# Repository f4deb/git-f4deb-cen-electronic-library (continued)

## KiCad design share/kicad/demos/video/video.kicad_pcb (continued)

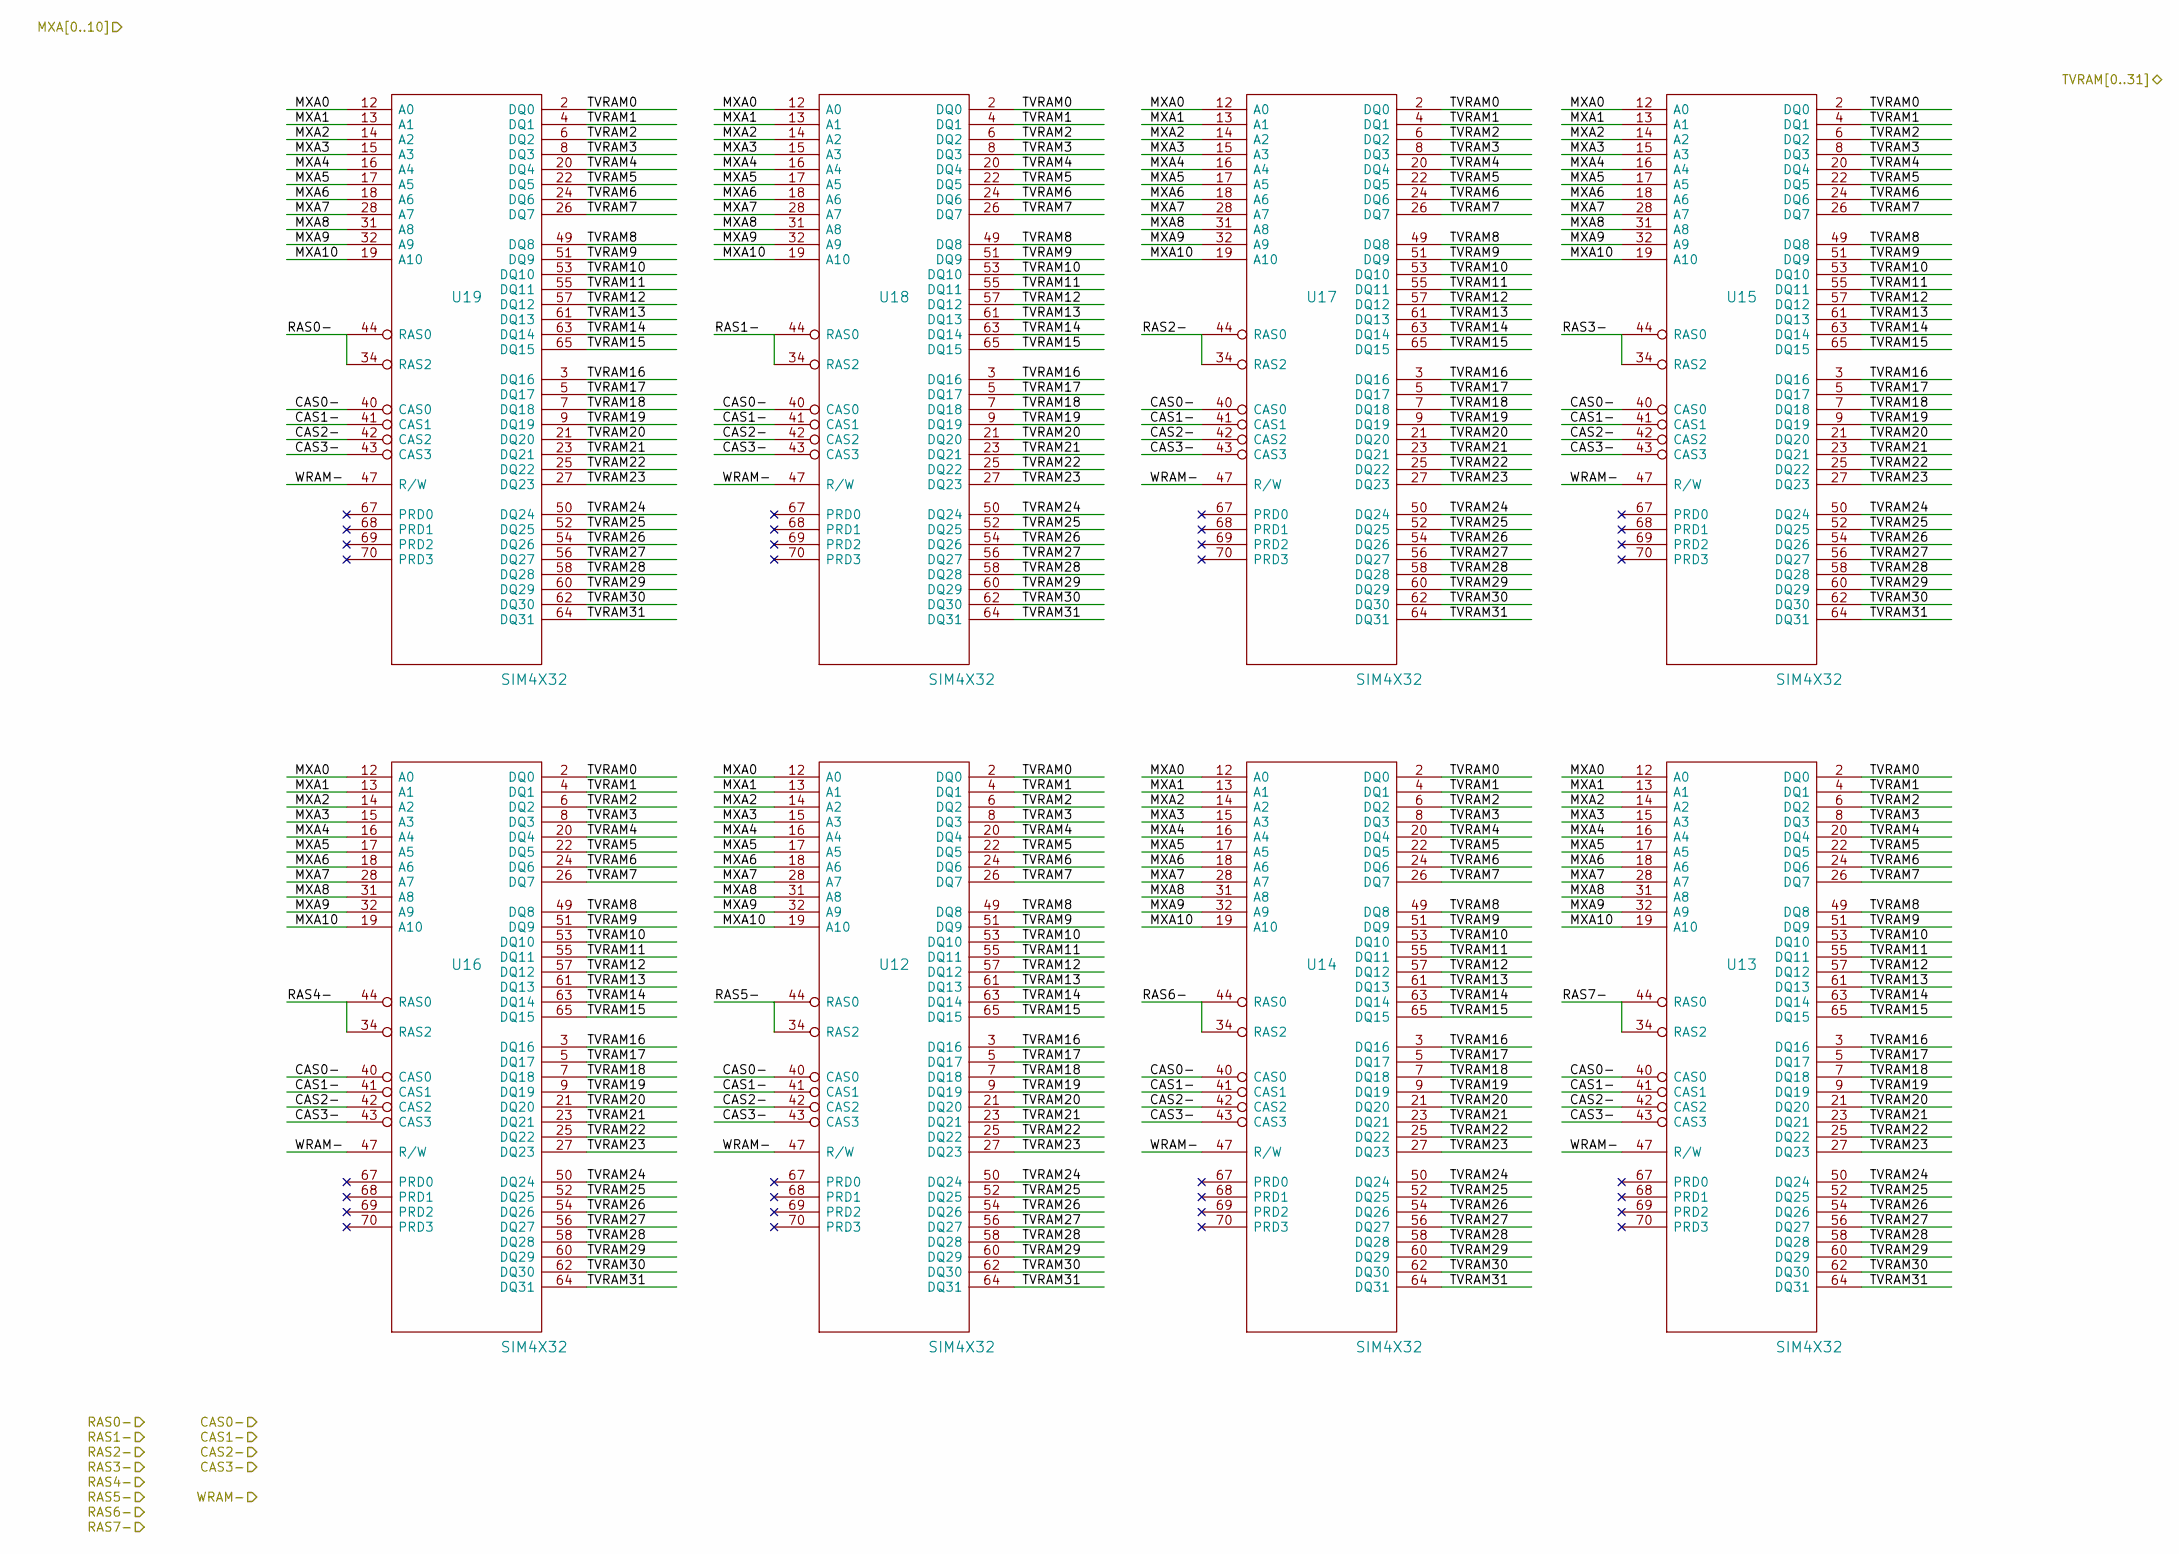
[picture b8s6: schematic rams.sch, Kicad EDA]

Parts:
U12, U13, U14, U15, U16, U17, U18, U19: SIM4X32; sim72

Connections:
/RAMS/CAS0-: U12.40 (CAS0), U13.40 (CAS0), U14.40 (CAS0), U15.40 (CAS0), U16.40 (CAS0), U17.40 (CAS0), U18.40 (CAS0), U19.40 (CAS0); also elsewhere on the board
/RAMS/CAS1-: U12.41 (CAS1), U13.41 (CAS1), U14.41 (CAS1), U15.41 (CAS1), U16.41 (CAS1), U17.41 (CAS1), U18.41 (CAS1), U19.41 (CAS1); also elsewhere on the board
/RAMS/CAS2-: U12.42 (CAS2), U13.42 (CAS2), U14.42 (CAS2), U15.42 (CAS2), U16.42 (CAS2), U17.42 (CAS2), U18.42 (CAS2), U19.42 (CAS2); also elsewhere on the board
/RAMS/CAS3-: U12.43 (CAS3), U13.43 (CAS3), U14.43 (CAS3), U15.43 (CAS3), U16.43 (CAS3), U17.43 (CAS3), U18.43 (CAS3), U19.43 (CAS3); also elsewhere on the board
/RAMS/MXA0: U12.12 (A0), U13.12 (A0), U14.12 (A0), U15.12 (A0), U16.12 (A0), U17.12 (A0), U18.12 (A0), U19.12 (A0); also elsewhere on the board
/RAMS/MXA1: U12.13 (A1), U13.13 (A1), U14.13 (A1), U15.13 (A1), U16.13 (A1), U17.13 (A1), U18.13 (A1), U19.13 (A1); also elsewhere on the board
/RAMS/MXA2: U12.14 (A2), U13.14 (A2), U14.14 (A2), U15.14 (A2), U16.14 (A2), U17.14 (A2), U18.14 (A2), U19.14 (A2); also elsewhere on the board
/RAMS/MXA3: U12.15 (A3), U13.15 (A3), U14.15 (A3), U15.15 (A3), U16.15 (A3), U17.15 (A3), U18.15 (A3), U19.15 (A3); also elsewhere on the board
/RAMS/MXA4: U12.16 (A4), U13.16 (A4), U14.16 (A4), U15.16 (A4), U16.16 (A4), U17.16 (A4), U18.16 (A4), U19.16 (A4); also elsewhere on the board
/RAMS/MXA5: U12.17 (A5), U13.17 (A5), U14.17 (A5), U15.17 (A5), U16.17 (A5), U17.17 (A5), U18.17 (A5), U19.17 (A5); also elsewhere on the board
/RAMS/MXA6: U12.18 (A6), U13.18 (A6), U14.18 (A6), U15.18 (A6), U16.18 (A6), U17.18 (A6), U18.18 (A6), U19.18 (A6); also elsewhere on the board
/RAMS/MXA7: U12.28 (A7), U13.28 (A7), U14.28 (A7), U15.28 (A7), U16.28 (A7), U17.28 (A7), U18.28 (A7), U19.28 (A7); also elsewhere on the board
/RAMS/MXA8: U12.31 (A8), U13.31 (A8), U14.31 (A8), U15.31 (A8), U16.31 (A8), U17.31 (A8), U18.31 (A8), U19.31 (A8); also elsewhere on the board
/RAMS/MXA9: U12.32 (A9), U13.32 (A9), U14.32 (A9), U15.32 (A9), U16.32 (A9), U17.32 (A9), U18.32 (A9), U19.32 (A9); also elsewhere on the board
/RAMS/MXA10: U12.19 (A10), U13.19 (A10), U14.19 (A10), U15.19 (A10), U16.19 (A10), U17.19 (A10), U18.19 (A10), U19.19 (A10); also elsewhere on the board
/RAMS/RAS0-: U19.34 (RAS2), U19.44 (RAS0); also elsewhere on the board
/RAMS/RAS1-: U18.34 (RAS2), U18.44 (RAS0); also elsewhere on the board
/RAMS/RAS2-: U17.34 (RAS2), U17.44 (RAS0); also elsewhere on the board
/RAMS/RAS3-: U15.34 (RAS2), U15.44 (RAS0); also elsewhere on the board
/RAMS/RAS4-: U16.34 (RAS2), U16.44 (RAS0); also elsewhere on the board
/RAMS/RAS5-: U12.34 (RAS2), U12.44 (RAS0); also elsewhere on the board
/RAMS/RAS6-: U14.34 (RAS2), U14.44 (RAS0); also elsewhere on the board
/RAMS/RAS7-: U13.34 (RAS2), U13.44 (RAS0); also elsewhere on the board
/RAMS/TVRAM0: U12.2 (DQ0), U13.2 (DQ0), U14.2 (DQ0), U15.2 (DQ0), U16.2 (DQ0), U17.2 (DQ0), U18.2 (DQ0), U19.2 (DQ0); also elsewhere on the board
/RAMS/TVRAM1: U12.4 (DQ1), U13.4 (DQ1), U14.4 (DQ1), U15.4 (DQ1), U16.4 (DQ1), U17.4 (DQ1), U18.4 (DQ1), U19.4 (DQ1); also elsewhere on the board
/RAMS/TVRAM2: U12.6 (DQ2), U13.6 (DQ2), U14.6 (DQ2), U15.6 (DQ2), U16.6 (DQ2), U17.6 (DQ2), U18.6 (DQ2), U19.6 (DQ2); also elsewhere on the board
/RAMS/TVRAM3: U12.8 (DQ3), U13.8 (DQ3), U14.8 (DQ3), U15.8 (DQ3), U16.8 (DQ3), U17.8 (DQ3), U18.8 (DQ3), U19.8 (DQ3); also elsewhere on the board
/RAMS/TVRAM4: U12.20 (DQ4), U13.20 (DQ4), U14.20 (DQ4), U15.20 (DQ4), U16.20 (DQ4), U17.20 (DQ4), U18.20 (DQ4), U19.20 (DQ4); also elsewhere on the board
/RAMS/TVRAM5: U12.22 (DQ5), U13.22 (DQ5), U14.22 (DQ5), U15.22 (DQ5), U16.22 (DQ5), U17.22 (DQ5), U18.22 (DQ5), U19.22 (DQ5); also elsewhere on the board
/RAMS/TVRAM6: U12.24 (DQ6), U13.24 (DQ6), U14.24 (DQ6), U15.24 (DQ6), U16.24 (DQ6), U17.24 (DQ6), U18.24 (DQ6), U19.24 (DQ6); also elsewhere on the board
/RAMS/TVRAM7: U12.26 (DQ7), U13.26 (DQ7), U14.26 (DQ7), U15.26 (DQ7), U16.26 (DQ7), U17.26 (DQ7), U18.26 (DQ7), U19.26 (DQ7); also elsewhere on the board
/RAMS/TVRAM8: U12.49 (DQ8), U13.49 (DQ8), U14.49 (DQ8), U15.49 (DQ8), U16.49 (DQ8), U17.49 (DQ8), U18.49 (DQ8), U19.49 (DQ8); also elsewhere on the board
/RAMS/TVRAM9: U12.51 (DQ9), U13.51 (DQ9), U14.51 (DQ9), U15.51 (DQ9), U16.51 (DQ9), U17.51 (DQ9), U18.51 (DQ9), U19.51 (DQ9); also elsewhere on the board
/RAMS/TVRAM10: U12.53 (DQ10), U13.53 (DQ10), U14.53 (DQ10), U15.53 (DQ10), U16.53 (DQ10), U17.53 (DQ10), U18.53 (DQ10), U19.53 (DQ10); also elsewhere on the board
/RAMS/TVRAM11: U12.55 (DQ11), U13.55 (DQ11), U14.55 (DQ11), U15.55 (DQ11), U16.55 (DQ11), U17.55 (DQ11), U18.55 (DQ11), U19.55 (DQ11); also elsewhere on the board
/RAMS/TVRAM12: U12.57 (DQ12), U13.57 (DQ12), U14.57 (DQ12), U15.57 (DQ12), U16.57 (DQ12), U17.57 (DQ12), U18.57 (DQ12), U19.57 (DQ12); also elsewhere on the board
/RAMS/TVRAM13: U12.61 (DQ13), U13.61 (DQ13), U14.61 (DQ13), U15.61 (DQ13), U16.61 (DQ13), U17.61 (DQ13), U18.61 (DQ13), U19.61 (DQ13); also elsewhere on the board
/RAMS/TVRAM14: U12.63 (DQ14), U13.63 (DQ14), U14.63 (DQ14), U15.63 (DQ14), U16.63 (DQ14), U17.63 (DQ14), U18.63 (DQ14), U19.63 (DQ14); also elsewhere on the board
/RAMS/TVRAM15: U12.65 (DQ15), U13.65 (DQ15), U14.65 (DQ15), U15.65 (DQ15), U16.65 (DQ15), U17.65 (DQ15), U18.65 (DQ15), U19.65 (DQ15); also elsewhere on the board
/RAMS/TVRAM16: U12.3 (DQ16), U13.3 (DQ16), U14.3 (DQ16), U15.3 (DQ16), U16.3 (DQ16), U17.3 (DQ16), U18.3 (DQ16), U19.3 (DQ16); also elsewhere on the board
/RAMS/TVRAM17: U12.5 (DQ17), U13.5 (DQ17), U14.5 (DQ17), U15.5 (DQ17), U16.5 (DQ17), U17.5 (DQ17), U18.5 (DQ17), U19.5 (DQ17); also elsewhere on the board
/RAMS/TVRAM18: U12.7 (DQ18), U13.7 (DQ18), U14.7 (DQ18), U15.7 (DQ18), U16.7 (DQ18), U17.7 (DQ18), U18.7 (DQ18), U19.7 (DQ18); also elsewhere on the board
/RAMS/TVRAM19: U12.9 (DQ19), U13.9 (DQ19), U14.9 (DQ19), U15.9 (DQ19), U16.9 (DQ19), U17.9 (DQ19), U18.9 (DQ19), U19.9 (DQ19); also elsewhere on the board
/RAMS/TVRAM20: U12.21 (DQ20), U13.21 (DQ20), U14.21 (DQ20), U15.21 (DQ20), U16.21 (DQ20), U17.21 (DQ20), U18.21 (DQ20), U19.21 (DQ20); also elsewhere on the board
/RAMS/TVRAM21: U12.23 (DQ21), U13.23 (DQ21), U14.23 (DQ21), U15.23 (DQ21), U16.23 (DQ21), U17.23 (DQ21), U18.23 (DQ21), U19.23 (DQ21); also elsewhere on the board
/RAMS/TVRAM22: U12.25 (DQ22), U13.25 (DQ22), U14.25 (DQ22), U15.25 (DQ22), U16.25 (DQ22), U17.25 (DQ22), U18.25 (DQ22), U19.25 (DQ22); also elsewhere on the board
/RAMS/TVRAM23: U12.27 (DQ23), U13.27 (DQ23), U14.27 (DQ23), U15.27 (DQ23), U16.27 (DQ23), U17.27 (DQ23), U18.27 (DQ23), U19.27 (DQ23); also elsewhere on the board
/RAMS/TVRAM24: U12.50 (DQ24), U13.50 (DQ24), U14.50 (DQ24), U15.50 (DQ24), U16.50 (DQ24), U17.50 (DQ24), U18.50 (DQ24), U19.50 (DQ24); also elsewhere on the board
/RAMS/TVRAM25: U12.52 (DQ25), U13.52 (DQ25), U14.52 (DQ25), U15.52 (DQ25), U16.52 (DQ25), U17.52 (DQ25), U18.52 (DQ25), U19.52 (DQ25); also elsewhere on the board
/RAMS/TVRAM26: U12.54 (DQ26), U13.54 (DQ26), U14.54 (DQ26), U15.54 (DQ26), U16.54 (DQ26), U17.54 (DQ26), U18.54 (DQ26), U19.54 (DQ26); also elsewhere on the board
/RAMS/TVRAM27: U12.56 (DQ27), U13.56 (DQ27), U14.56 (DQ27), U15.56 (DQ27), U16.56 (DQ27), U17.56 (DQ27), U18.56 (DQ27), U19.56 (DQ27); also elsewhere on the board
/RAMS/TVRAM28: U12.58 (DQ28), U13.58 (DQ28), U14.58 (DQ28), U15.58 (DQ28), U16.58 (DQ28), U17.58 (DQ28), U18.58 (DQ28), U19.58 (DQ28); also elsewhere on the board
/RAMS/TVRAM29: U12.60 (DQ29), U13.60 (DQ29), U14.60 (DQ29), U15.60 (DQ29), U16.60 (DQ29), U17.60 (DQ29), U18.60 (DQ29), U19.60 (DQ29); also elsewhere on the board
/RAMS/TVRAM30: U12.62 (DQ30), U13.62 (DQ30), U14.62 (DQ30), U15.62 (DQ30), U16.62 (DQ30), U17.62 (DQ30), U18.62 (DQ30), U19.62 (DQ30); also elsewhere on the board
/RAMS/TVRAM31: U12.64 (DQ31), U13.64 (DQ31), U14.64 (DQ31), U15.64 (DQ31), U16.64 (DQ31), U17.64 (DQ31), U18.64 (DQ31), U19.64 (DQ31); also elsewhere on the board
/RAMS/WRAM-: U12.47 (R/W), U13.47 (R/W), U14.47 (R/W), U15.47 (R/W), U16.47 (R/W), U17.47 (R/W), U18.47 (R/W), U19.47 (R/W); also elsewhere on the board
GND: U12.1 (GND), U12.39 (GND), U12.72 (GND), U13.1 (GND), U13.39 (GND), U13.72 (GND), U14.1 (GND), U14.39 (GND), U14.72 (GND), U15.1 (GND), U15.39 (GND), U15.72 (GND), U16.1 (GND), U16.39 (GND), U16.72 (GND), U17.1 (GND), U17.39 (GND), U17.72 (GND), U18.1 (GND), U18.39 (GND), U18.72 (GND), U19.1 (GND), U19.39 (GND), U19.72 (GND); also elsewhere on the board
VCC: U12.10 (VCC), U12.30 (VCC), U12.59 (VCC), U13.10 (VCC), U13.30 (VCC), U13.59 (VCC), U14.10 (VCC), U14.30 (VCC), U14.59 (VCC), U15.10 (VCC), U15.30 (VCC), U15.59 (VCC), U16.10 (VCC), U16.30 (VCC), U16.59 (VCC), U17.10 (VCC), U17.30 (VCC), U17.59 (VCC), U18.10 (VCC), U18.30 (VCC), U18.59 (VCC), U19.10 (VCC), U19.30 (VCC), U19.59 (VCC); also elsewhere on the board

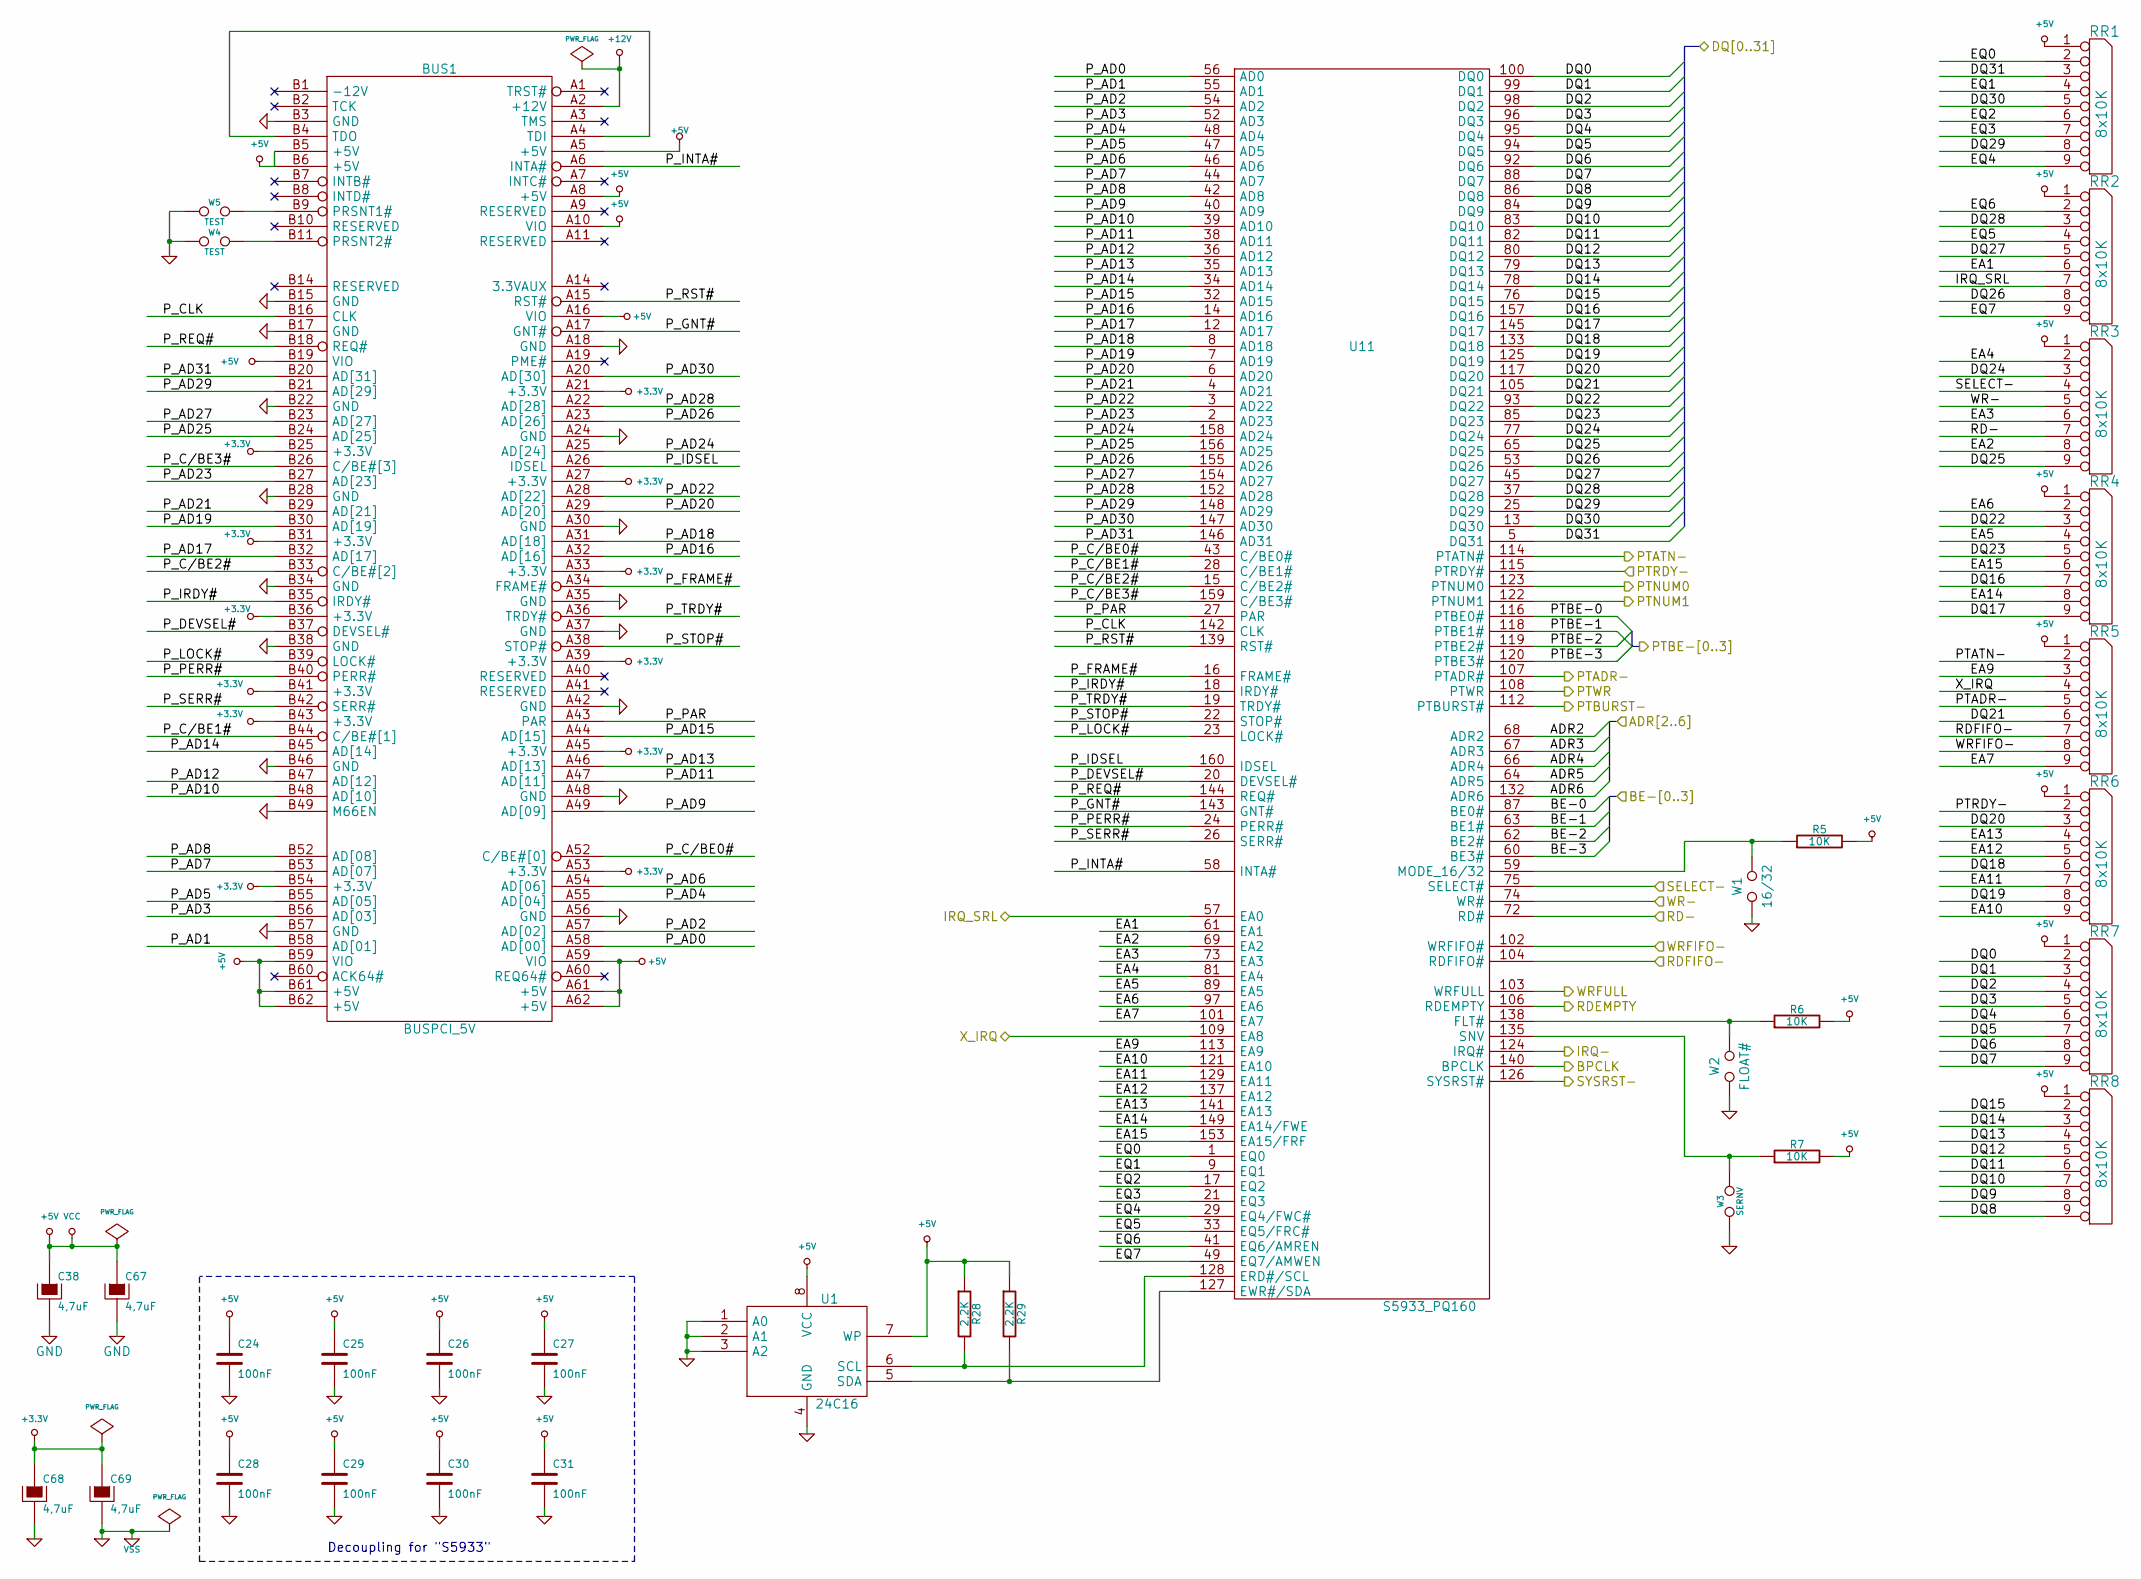
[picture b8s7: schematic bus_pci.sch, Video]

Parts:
BUS1: BUSPCI_5V; BUSPCI
C24, C25, C26, C27, C28, C29, C30, C31: 100nF; SM1206
C38: 4,7uF; SM1812L
C67, C68, C69: 4,7uF; SM1206
R5, R6, R7: 10K; SM1206
R28, R29: 2,2K; SM1206
RR1, RR2, RR3, RR6, RR8: 8x10K; SIL-9
RR4, RR5, RR7: 8x10K; r_pack8
U1: 24C16; DIP-8__300
U11: S5933_PQ160; PQFP160
W1: 16/32; GS2
W2: FLOAT#; GS2
W3: SERNV; GS2
W4, W5: TEST; PIN_ARRAY_2X1

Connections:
+3.3V: BUS1.A21 (+3.3V), BUS1.A27 (+3.3V), BUS1.A33 (+3.3V), BUS1.A39 (+3.3V), BUS1.A45 (+3.3V), BUS1.A53 (+3.3V), BUS1.B25 (+3.3V), BUS1.B31 (+3.3V), BUS1.B36 (+3.3V), BUS1.B41 (+3.3V), BUS1.B43 (+3.3V), BUS1.B54 (+3.3V), C68.1, C69.1
+12V: BUS1.A2 (+12V)
/ESVIDEO-RVB/DPC0: RR7.2, U11.100 (DQ0); also elsewhere on the board
/ESVIDEO-RVB/DPC1: RR7.3, U11.99 (DQ1); also elsewhere on the board
/ESVIDEO-RVB/DPC2: RR7.4, U11.98 (DQ2); also elsewhere on the board
/ESVIDEO-RVB/DPC3: RR7.5, U11.96 (DQ3); also elsewhere on the board
/ESVIDEO-RVB/DPC4: RR7.6, U11.95 (DQ4); also elsewhere on the board
/ESVIDEO-RVB/DPC5: RR7.7, U11.94 (DQ5); also elsewhere on the board
/ESVIDEO-RVB/DPC6: RR7.8, U11.92 (DQ6); also elsewhere on the board
/ESVIDEO-RVB/DPC7: RR7.9, U11.88 (DQ7); also elsewhere on the board
/buspci.sch/ADR2: U11.68 (ADR2); also elsewhere on the board
/buspci.sch/ADR3: U11.67 (ADR3); also elsewhere on the board
/buspci.sch/ADR4: U11.66 (ADR4); also elsewhere on the board
/buspci.sch/ADR5: U11.64 (ADR5); also elsewhere on the board
/buspci.sch/ADR6: U11.132 (ADR6); also elsewhere on the board
/buspci.sch/BE-0: U11.87 (BE0#); also elsewhere on the board
/buspci.sch/BE-1: U11.63 (BE1#); also elsewhere on the board
/buspci.sch/BE-2: U11.62 (BE2#); also elsewhere on the board
/buspci.sch/BE-3: U11.60 (BE3#); also elsewhere on the board
/buspci.sch/BPCLK: U11.140 (BPCLK); also elsewhere on the board
/buspci.sch/EA1: RR2.6, U11.61 (EA1)
/buspci.sch/EA2: RR3.8, U11.69 (EA2)
/buspci.sch/EA3: RR3.6, U11.73 (EA3)
/buspci.sch/EA4: RR3.2, U11.81 (EA4)
/buspci.sch/EA5: RR4.4, U11.89 (EA5)
/buspci.sch/EA6: RR4.2, U11.97 (EA6)
/buspci.sch/EA7: RR5.9, U11.101 (EA7)
/buspci.sch/EA9: RR5.3, U11.113 (EA9)
/buspci.sch/EA10: RR6.9, U11.121 (EA10)
/buspci.sch/EA11: RR6.7, U11.129 (EA11)
/buspci.sch/EA12: RR6.5, U11.137 (EA12)
/buspci.sch/EA13: RR6.4, U11.141 (EA13)
/buspci.sch/EA14: RR4.8, U11.149 (EA14/FWE)
/buspci.sch/EA15: RR4.6, U11.153 (EA15/FRF)
/buspci.sch/EQ0: RR1.2, U11.1 (EQ0)
/buspci.sch/EQ1: RR1.4, U11.9 (EQ1)
/buspci.sch/EQ2: RR1.6, U11.17 (EQ2)
/buspci.sch/EQ3: RR1.7, U11.21 (EQ3)
/buspci.sch/EQ4: RR1.9, U11.29 (EQ4/FWC#)
/buspci.sch/EQ5: RR2.4, U11.33 (EQ5/FRC#)
/buspci.sch/EQ6: RR2.2, U11.41 (EQ6/AMREN)
/buspci.sch/EQ7: RR2.9, U11.49 (EQ7/AMWEN)
/buspci.sch/IRQ-: U11.124 (IRQ#); also elsewhere on the board
/buspci.sch/PTADR-: RR5.5, U11.107 (PTADR#); also elsewhere on the board
/buspci.sch/PTATN-: RR5.2, U11.114 (PTATN#); also elsewhere on the board
/buspci.sch/PTBE-0: U11.116 (PTBE0#); also elsewhere on the board
/buspci.sch/PTBE-1: U11.118 (PTBE1#); also elsewhere on the board
/buspci.sch/PTBE-2: U11.119 (PTBE2#); also elsewhere on the board
/buspci.sch/PTBE-3: U11.120 (PTBE3#); also elsewhere on the board
/buspci.sch/PTBURST-: U11.112 (PTBURST#); also elsewhere on the board
/buspci.sch/PTNUM0: U11.123 (PTNUM0); also elsewhere on the board
/buspci.sch/PTNUM1: U11.122 (PTNUM1); also elsewhere on the board
/buspci.sch/PTRDY-: RR6.2, U11.115 (PTRDY#); also elsewhere on the board
/buspci.sch/PTWR: U11.108 (PTWR); also elsewhere on the board
/buspci.sch/P_AD0: BUS1.A58 (AD[00]), U11.56 (AD0)
/buspci.sch/P_AD1: BUS1.B58 (AD[01]), U11.55 (AD1)
/buspci.sch/P_AD2: BUS1.A57 (AD[02]), U11.54 (AD2)
/buspci.sch/P_AD3: BUS1.B56 (AD[03]), U11.52 (AD3)
/buspci.sch/P_AD4: BUS1.A55 (AD[04]), U11.48 (AD4)
/buspci.sch/P_AD5: BUS1.B55 (AD[05]), U11.47 (AD5)
/buspci.sch/P_AD6: BUS1.A54 (AD[06]), U11.46 (AD6)
/buspci.sch/P_AD7: BUS1.B53 (AD[07]), U11.44 (AD7)
/buspci.sch/P_AD8: BUS1.B52 (AD[08]), U11.42 (AD8)
/buspci.sch/P_AD9: BUS1.A49 (AD[09]), U11.40 (AD9)
/buspci.sch/P_AD10: BUS1.B48 (AD[10]), U11.39 (AD10)
/buspci.sch/P_AD11: BUS1.A47 (AD[11]), U11.38 (AD11)
/buspci.sch/P_AD12: BUS1.B47 (AD[12]), U11.36 (AD12)
/buspci.sch/P_AD13: BUS1.A46 (AD[13]), U11.35 (AD13)
/buspci.sch/P_AD14: BUS1.B45 (AD[14]), U11.34 (AD14)
/buspci.sch/P_AD15: BUS1.A44 (AD[15]), U11.32 (AD15)
/buspci.sch/P_AD16: BUS1.A32 (AD[16]), U11.14 (AD16)
/buspci.sch/P_AD17: BUS1.B32 (AD[17]), U11.12 (AD17)
/buspci.sch/P_AD18: BUS1.A31 (AD[18]), U11.8 (AD18)
/buspci.sch/P_AD19: BUS1.B30 (AD[19]), U11.7 (AD19)
/buspci.sch/P_AD20: BUS1.A29 (AD[20]), U11.6 (AD20)
/buspci.sch/P_AD21: BUS1.B29 (AD[21]), U11.4 (AD21)
/buspci.sch/P_AD22: BUS1.A28 (AD[22]), U11.3 (AD22)
/buspci.sch/P_AD23: BUS1.B27 (AD[23]), U11.2 (AD23)
/buspci.sch/P_AD24: BUS1.A25 (AD[24]), U11.158 (AD24)
/buspci.sch/P_AD25: BUS1.B24 (AD[25]), U11.156 (AD25)
/buspci.sch/P_AD26: BUS1.A23 (AD[26]), U11.155 (AD26)
/buspci.sch/P_AD27: BUS1.B23 (AD[27]), U11.154 (AD27)
/buspci.sch/P_AD28: BUS1.A22 (AD[28]), U11.152 (AD28)
/buspci.sch/P_AD29: BUS1.B21 (AD[29]), U11.148 (AD29)
/buspci.sch/P_AD30: BUS1.A20 (AD[30]), U11.147 (AD30)
/buspci.sch/P_AD31: BUS1.B20 (AD[31]), U11.146 (AD31)
/buspci.sch/P_C/BE0#: BUS1.A52 (C/BE#[0]), U11.43 (C/BE0#)
/buspci.sch/P_C/BE1#: BUS1.B44 (C/BE#[1]), U11.28 (C/BE1#)
/buspci.sch/P_C/BE2#: BUS1.B33 (C/BE#[2]), U11.15 (C/BE2#)
/buspci.sch/P_C/BE3#: BUS1.B26 (C/BE#[3]), U11.159 (C/BE3#)
/buspci.sch/P_CLK: BUS1.B16 (CLK), U11.142 (CLK)
/buspci.sch/P_DEVSEL#: BUS1.B37 (DEVSEL#), U11.20 (DEVSEL#)
/buspci.sch/P_FRAME#: BUS1.A34 (FRAME#), U11.16 (FRAME#)
/buspci.sch/P_GNT#: BUS1.A17 (GNT#), U11.143 (GNT#)
/buspci.sch/P_IDSEL: BUS1.A26 (IDSEL), U11.160 (IDSEL)
/buspci.sch/P_INTA#: BUS1.A6 (INTA#), U11.58 (INTA#)
/buspci.sch/P_IRDY#: BUS1.B35 (IRDY#), U11.18 (IRDY#)
/buspci.sch/P_LOCK#: BUS1.B39 (LOCK#), U11.23 (LOCK#)
/buspci.sch/P_PAR: BUS1.A43 (PAR), U11.27 (PAR)
/buspci.sch/P_PERR#: BUS1.B40 (PERR#), U11.24 (PERR#)
/buspci.sch/P_REQ#: BUS1.B18 (REQ#), U11.144 (REQ#)
/buspci.sch/P_RST#: BUS1.A15 (RST#), U11.139 (RST#)
/buspci.sch/P_SERR#: BUS1.B42 (SERR#), U11.26 (SERR#)
/buspci.sch/P_STOP#: BUS1.A38 (STOP#), U11.22 (STOP#)
/buspci.sch/P_TRDY#: BUS1.A36 (TRDY#), U11.19 (TRDY#)
/buspci.sch/RD-: RR3.7, U11.72 (RD#); also elsewhere on the board
/buspci.sch/RDEMPTY: U11.106 (RDEMPTY); also elsewhere on the board
/buspci.sch/RDFIFO-: RR5.7, U11.104 (RDFIFO#); also elsewhere on the board
/buspci.sch/SELECT-: RR3.4, U11.75 (SELECT#); also elsewhere on the board
/buspci.sch/WR-: RR3.5, U11.74 (WR#); also elsewhere on the board
/buspci.sch/WRFIFO-: RR5.8, U11.102 (WRFIFO#); also elsewhere on the board
/buspci.sch/WRFULL: U11.103 (WRFULL); also elsewhere on the board
/buspci.sch/X_IRQ: RR5.4, U11.109 (EA8); also elsewhere on the board
/graphic/IRQ_SLR: RR2.7, U11.57 (EA0); also elsewhere on the board
/muxdata/DPC8: RR8.9, U11.86 (DQ8); also elsewhere on the board
/muxdata/DPC9: RR8.8, U11.84 (DQ9); also elsewhere on the board
/muxdata/DPC10: RR8.7, U11.83 (DQ10); also elsewhere on the board
/muxdata/DPC11: RR8.6, U11.82 (DQ11); also elsewhere on the board
/muxdata/DPC12: RR8.5, U11.80 (DQ12); also elsewhere on the board
/muxdata/DPC13: RR8.4, U11.79 (DQ13); also elsewhere on the board
/muxdata/DPC14: RR8.3, U11.78 (DQ14); also elsewhere on the board
/muxdata/DPC15: RR8.2, U11.76 (DQ15); also elsewhere on the board
/muxdata/DPC16: RR4.7, U11.157 (DQ16); also elsewhere on the board
/muxdata/DPC17: RR4.9, U11.145 (DQ17); also elsewhere on the board
/muxdata/DPC18: RR6.6, U11.133 (DQ18); also elsewhere on the board
/muxdata/DPC19: RR6.8, U11.125 (DQ19); also elsewhere on the board
/muxdata/DPC20: RR6.3, U11.117 (DQ20); also elsewhere on the board
/muxdata/DPC21: RR5.6, U11.105 (DQ21); also elsewhere on the board
/muxdata/DPC22: RR4.3, U11.93 (DQ22); also elsewhere on the board
/muxdata/DPC23: RR4.5, U11.85 (DQ23); also elsewhere on the board
/muxdata/DPC24: RR3.3, U11.77 (DQ24); also elsewhere on the board
/muxdata/DPC25: RR3.9, U11.65 (DQ25); also elsewhere on the board
/muxdata/DPC26: RR2.8, U11.53 (DQ26); also elsewhere on the board
/muxdata/DPC27: RR2.5, U11.45 (DQ27); also elsewhere on the board
/muxdata/DPC28: RR2.3, U11.37 (DQ28); also elsewhere on the board
/muxdata/DPC29: RR1.8, U11.25 (DQ29); also elsewhere on the board
/muxdata/DPC30: RR1.5, U11.13 (DQ30); also elsewhere on the board
/muxdata/DPC31: RR1.3, U11.5 (DQ31); also elsewhere on the board
/pal-ntsc.sch/RESET-: U11.126 (SYSRST#); also elsewhere on the board
GND: BUS1.A18 (GND), BUS1.A24 (GND), BUS1.A30 (GND), BUS1.A35 (GND), BUS1.A37 (GND), BUS1.A42 (GND), BUS1.A48 (GND), BUS1.A56 (GND), BUS1.B3 (GND), BUS1.B15 (GND), BUS1.B17 (GND), BUS1.B22 (GND), BUS1.B28 (GND), BUS1.B34 (GND), BUS1.B38 (GND), BUS1.B46 (GND), BUS1.B49 (M66EN), BUS1.B57 (GND), C24.2, C25.2, C26.2, C27.2, C28.2, C29.2, C30.2, C31.2, C38.2, C67.2, C68.2, C69.2, U1.1 (A0), U1.2 (A1), U1.3 (A2), U1.4 (GND), U11.10 (VSS), U11.30 (VSS), U11.50 (VSS), U11.70 (VSS), U11.90 (VSS), U11.110 (VSS), U11.130 (VSS), U11.150 (VSS), W1.1, W2.1, W3.1, W4.1, W5.1; also elsewhere on the board
unnamed: BUS1.A4 (TDI), BUS1.B4 (TDO)
unnamed: BUS1.B9 (PRSNT1#), W5.2
unnamed: BUS1.B11 (PRSNT2#), W4.2
unnamed: R5.1, U11.59 (MODE_16/32), W1.2
unnamed: R6.1, U11.138 (FLT#), W2.2
unnamed: R7.1, U11.135 (SNV), W3.2
unnamed: R28.2, U1.6 (SCL), U11.128 (ERD#/SCL)
unnamed: R29.2, U1.5 (SDA), U11.127 (EWR#/SDA)
VCC: BUS1.A5 (+5V), BUS1.A8 (+5V), BUS1.A10 (VIO), BUS1.A16 (VIO), BUS1.A59 (VIO), BUS1.A61 (+5V), BUS1.A62 (+5V), BUS1.B5 (+5V), BUS1.B6 (+5V), BUS1.B19 (VIO), BUS1.B59 (VIO), BUS1.B61 (+5V), BUS1.B62 (+5V), C24.1, C25.1, C26.1, C27.1, C28.1, C29.1, C30.1, C31.1, C38.1, C67.1, R5.2, R6.2, R7.2, R28.1, R29.1, RR1.1 (COM), RR2.1 (COM), RR3.1 (COM), RR4.1 (COM), RR5.1 (COM), RR6.1 (COM), RR7.1 (COM), RR8.1 (COM), U1.7 (WP), U1.8 (VCC), U11.11 (VCC), U11.31 (VCC), U11.51 (VCC), U11.71 (VCC), U11.91 (VCC), U11.111 (VCC), U11.131 (VCC), U11.151 (VCC); also elsewhere on the board

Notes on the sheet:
Decoupling for "S5933"
